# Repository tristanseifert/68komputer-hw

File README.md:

# 68komputer Hardware
Hardware designs for the 68komputer.

You can find the related software [in this repository.](https://github.com/tristanseifert/68komputer-sw)

## Old stuff
The 68008-based design I [wrote about](https://blraaz.me/hardware/2019/11/01/68komputer-it-lives.html) and some other stuff has been moved to the `old` directory. Unfortunately, those designs were done using Cadsoft EAGLE, and I no longer have access to my license for it. There are likely hardware bugs I have no way of fixing. Yay!

## License
The contents of this repo are available under the ISC license.

Previously, the material in the `old` directory was BSD licensed; you can continue to use it under the terms of this license.

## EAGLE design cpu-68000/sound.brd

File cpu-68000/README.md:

# 68000 CPU Board
This directory contains the schematic and board files for the main 68komputer CPU board, based around a 68000 operating at up to 10MHz. It combines the processor with 1M of RAM and flash ROM and some additional peripherals.

## Peripherals
In addition to the megabyte of boot ROM and RAM available on the board, the following peripherals are available:

- 32K of battery backed NVRAM, which includes a phantom RTC for time keeping
- An [XR68C681](https://www.maxlinear.com/product/interface/uarts/8-bit-vlio-uarts/xr68c681) DUART, compatible with the "legacy" Motorola 68681 part
- I²C master provided by a [PCF8584](https://www.nxp.com/products/interfaces/ic-spi-serial-interface-devices/ic-bus-controller-and-bridge-ics/ic-bus-controller:PCF8584) controller. It's used to access the I2C bus on the backplane.
- Dual SAA1099 PSG audio chips

## Backplane Interface
The backplane interface is just a buffered copy of the 68k's address and data bus, as well as many of its control signals. The direction of buffers on the CPU board are automatically controlled taking into account external bus masters.

As long as external bus masters properly implement the 68000 bus mastering, they will be entirely transparent. All read/write transactions to peripherals implemented on the CPU board itself will be broadcast on the backplane bus to allow external debugging hardware to capture these accesses.

## Programmable Logic
Many of the logic parts of the system are implemented in 22V10C GALs. See the `logic` directory for these files. They can be assembled using [galette.](https://github.com/simon-frankau/galette)

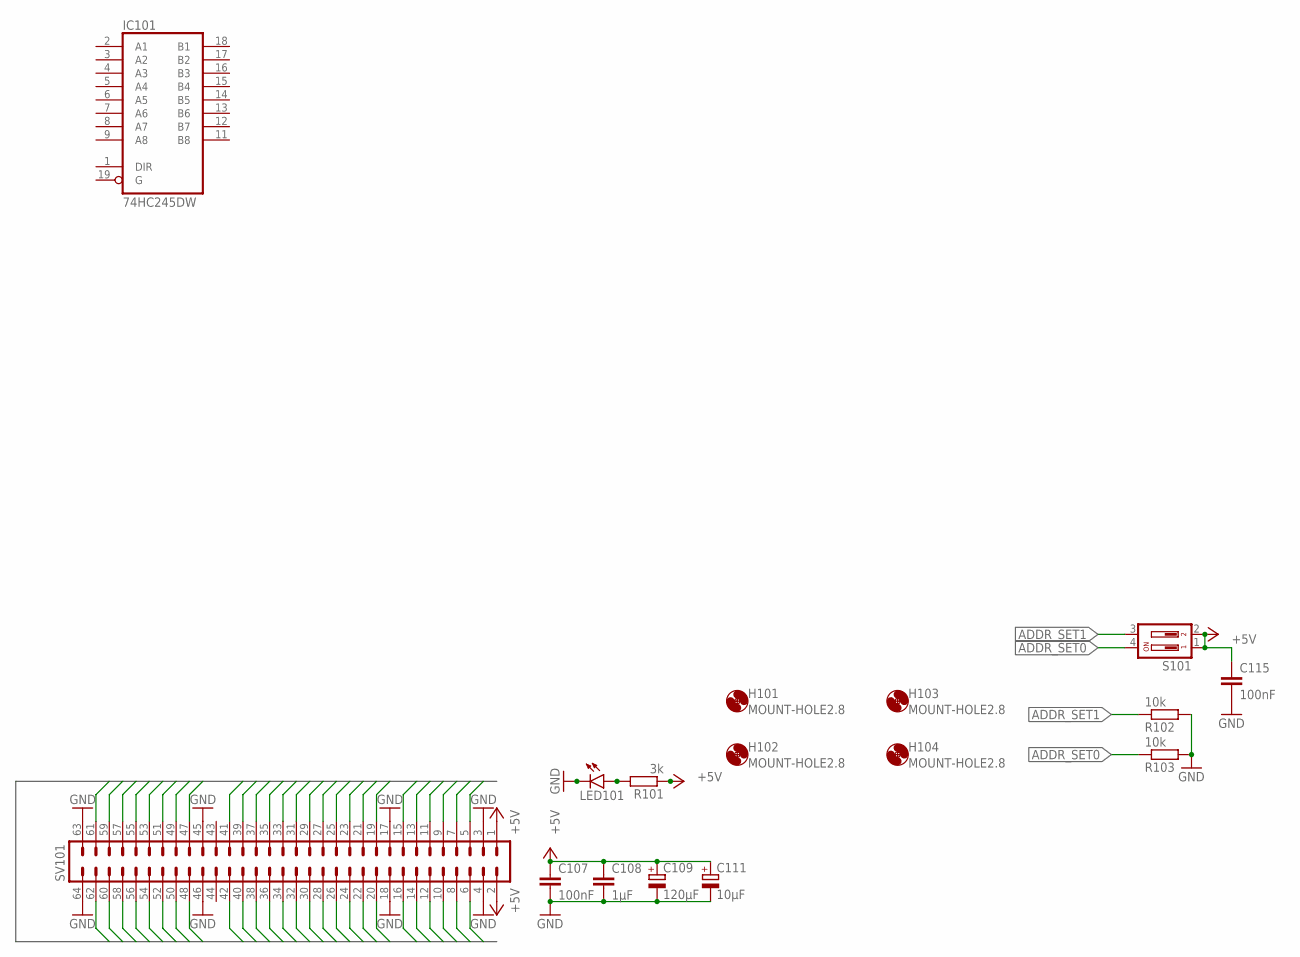
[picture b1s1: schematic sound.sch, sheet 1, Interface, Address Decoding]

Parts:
C107, C115: 100nF; C0805; MOUSER 710-885012207072
C108: 1µF; C0805; MOUSER 710-885012207078
C109: 120µF; E2,5-7; MOUSER 710-860020373007
C111: 10µF; SMC_B; MOUSER 581-TAJB106K020RNJV
H101, H102, H103, H104: MOUNT-HOLE2.8; 2,8
IC101: 74HC245DW; SO20W; MOUSER 595-SN74HC245DWR
LED101: LEDCHIPLED_1206; CHIPLED_1206; MOUSER 710-156120YS75300
R101: 3k; R2012; MOUSER 652-CR0805JW-302ELF
R102, R103: 10k; R2012; MOUSER 652-CR0805FX-1002ELF
S101: DP02; DP-02
SV101: ML64L

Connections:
!AS: SV101.13
!BG: SV101.9
!BGACK: SV101.8
!BR: SV101.7
!DTACK: SV101.10
!EXTI_A: SV101.16
!EXTI_B: SV101.15
!EXT_ID: SV101.41
!HALT: SV101.5
!LDS: SV101.11
!RESET: SV101.6
!UDS: SV101.14
+5V: C107.1, C108.1, C109.+, C111.+, C115.1, R101.1, S101.1, S101.2, SV101.1, SV101.2; also elsewhere on the board
A1: SV101.20
A2: SV101.22
A3: SV101.19
A4: SV101.24
A5: SV101.21
A6: SV101.23
A7: SV101.26
A8: SV101.25
A9: SV101.28
A10: SV101.27
A11: SV101.30
A12: SV101.29
A13: SV101.31
A14: SV101.32
A15: SV101.33
A16: SV101.34
A17: SV101.36
A18: SV101.35
A19: SV101.38
A20: SV101.37
A21: SV101.40
A22: SV101.39
A23: SV101.42
ADDR_SET0: R103.1, S101.4
ADDR_SET1: R102.1, S101.3
D0: SV101.62
D1: SV101.60
D2: SV101.58
D3: SV101.56
D4: SV101.54
D5: SV101.52
D6: SV101.50
D7: SV101.48
D8: SV101.57
D9: SV101.59
D10: SV101.61
D11: SV101.55
D12: SV101.53
D13: SV101.51
D14: SV101.49
D15: SV101.47
GND: C107.2, C108.2, C109.-, C111.-, C115.2, IC101.10 (GND), LED101.C, R102.2, R103.2, SV101.3, SV101.4, SV101.17, SV101.18, SV101.45, SV101.46, SV101.63, SV101.64; also elsewhere on the board
unnamed: LED101.A, R101.2
R/!W!: SV101.12
VCC: IC101.20 (VCC)

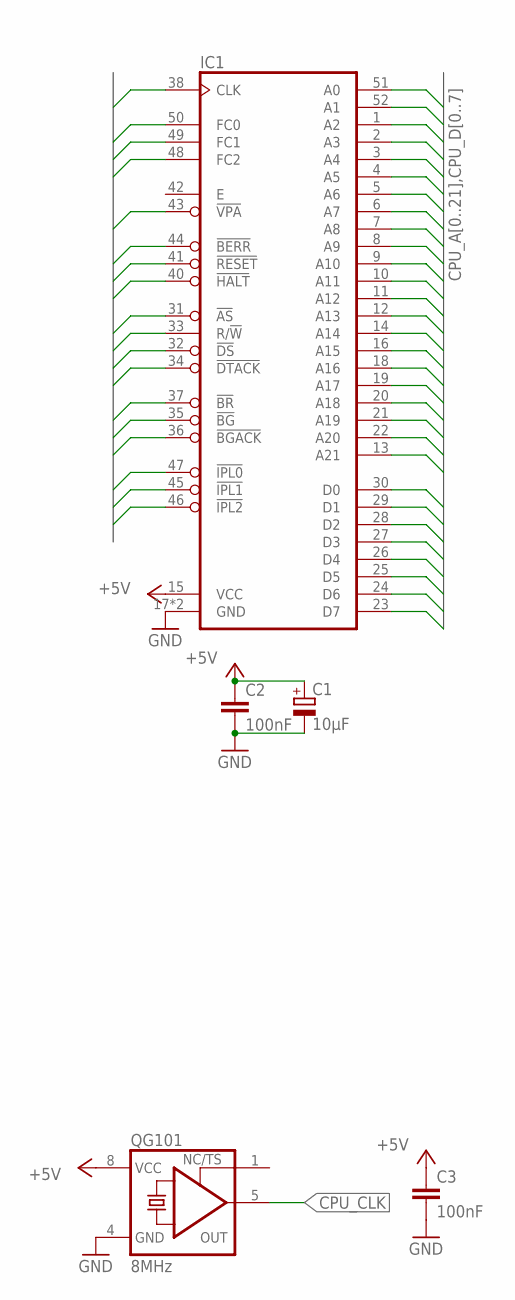
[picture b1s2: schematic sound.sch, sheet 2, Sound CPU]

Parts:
C1: 10µF; SMC_B; MOUSER 581-TAJB106K020RNJV
C2, C3: 100nF; C0805; MOUSER 710-885012207072
IC1: MC68008-PLCCPLCC52-SOCKET; PLCC52-S
QG101: 8MHz; DIL08S; MOUSER 774-MXO45HS-3C-8.0

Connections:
!CPU_AS: IC1.31 (!AS)
!CPU_BERR: IC1.44 (!BERR)
!CPU_BG: IC1.35 (!BG)
!CPU_BGACK: IC1.36 (!BGACK)
!CPU_BR: IC1.37 (!BR)
!CPU_DS: IC1.32 (!DS)
!CPU_DTACK: IC1.34 (!DTACK)
!CPU_HALT: IC1.40 (!HALT)
!CPU_IPL0: IC1.47 (!IPL0)
!CPU_IPL1: IC1.45 (!IPL1)
!CPU_IPL2: IC1.46 (!IPL2)
!CPU_RESET: IC1.41 (!RESET)
!CPU_VPA: IC1.43 (!VPA)
+5V: C1.+, C2.1, C3.1, IC1.15 (VCC), QG101.8 (VCC); also elsewhere on the board
CPU_A0: IC1.51 (A0)
CPU_A1: IC1.52 (A1)
CPU_A2: IC1.1 (A2)
CPU_A3: IC1.2 (A3)
CPU_A4: IC1.3 (A4)
CPU_A5: IC1.4 (A5)
CPU_A6: IC1.5 (A6)
CPU_A7: IC1.6 (A7)
CPU_A8: IC1.7 (A8)
CPU_A9: IC1.8 (A9)
CPU_A10: IC1.9 (A10)
CPU_A11: IC1.10 (A11)
CPU_A12: IC1.11 (A12)
CPU_A13: IC1.12 (A13)
CPU_A14: IC1.14 (A14)
CPU_A15: IC1.16 (A15)
CPU_A16: IC1.18 (A16)
CPU_A17: IC1.19 (A17)
CPU_A18: IC1.20 (A18)
CPU_A19: IC1.21 (A19)
CPU_A20: IC1.22 (A20)
CPU_A21: IC1.13 (A21)
CPU_CLK: IC1.38 (CLK), QG101.5 (OUT)
CPU_D0: IC1.30 (D0)
CPU_D1: IC1.29 (D1)
CPU_D2: IC1.28 (D2)
CPU_D3: IC1.27 (D3)
CPU_D4: IC1.26 (D4)
CPU_D5: IC1.25 (D5)
CPU_D6: IC1.24 (D6)
CPU_D7: IC1.23 (D7)
CPU_FC0: IC1.50 (FC0)
CPU_FC1: IC1.49 (FC1)
CPU_FC2: IC1.48 (FC2)
CPU_R/!W!: IC1.33 (R/!W)
GND: C1.-, C2.2, C3.2, IC1.17 (GND), IC1.39 (GND), QG101.4 (GND); also elsewhere on the board

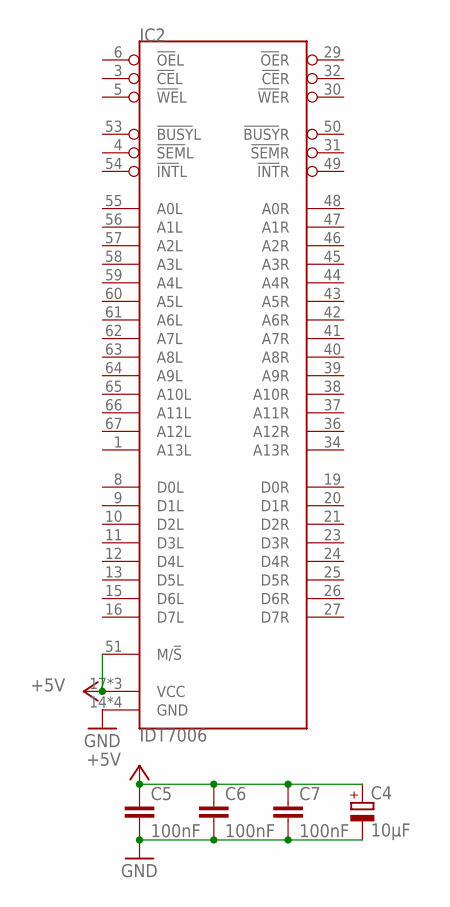
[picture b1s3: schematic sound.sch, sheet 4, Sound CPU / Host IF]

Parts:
C4: 10µF; SMC_B; MOUSER 581-TAJB106K020RNJV
C5, C6, C7: 100nF; C0805; MOUSER 710-885012207072
IC2: IDT7006; PLCC68-S

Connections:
+5V: C4.+, C5.1, C6.1, C7.1, IC2.17 (VCC), IC2.22 (VCC), IC2.51 (M/!S!), IC2.68 (VCC); also elsewhere on the board
GND: C4.-, C5.2, C6.2, C7.2, IC2.14 (GND), IC2.18 (GND), IC2.35 (GND), IC2.52 (GND); also elsewhere on the board

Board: 2 copper layers, 26 parts (3 on the bottom side), 6 nets, no tracks yet.

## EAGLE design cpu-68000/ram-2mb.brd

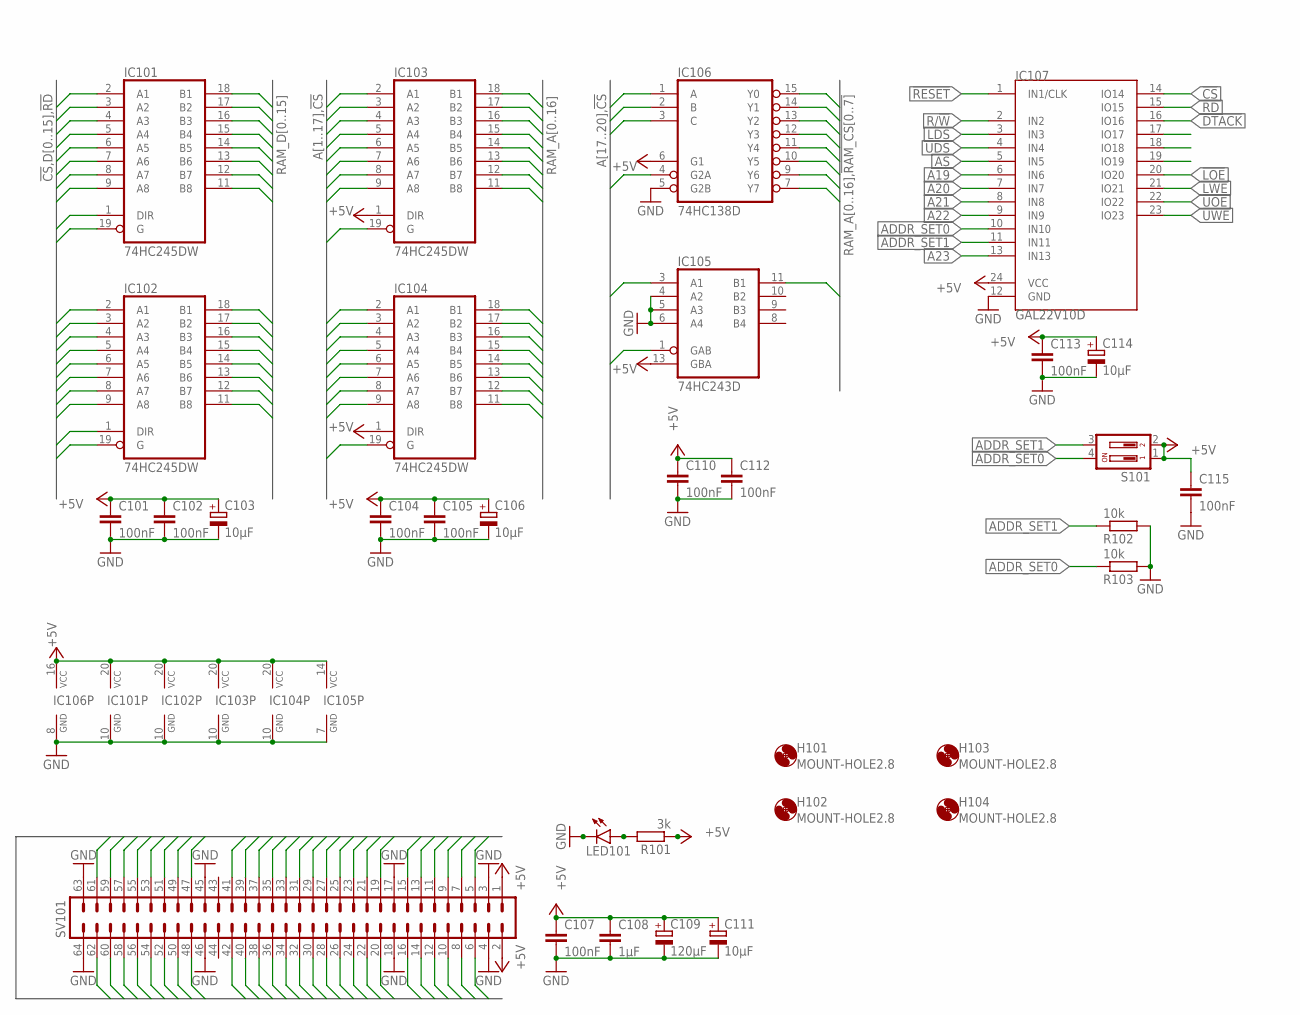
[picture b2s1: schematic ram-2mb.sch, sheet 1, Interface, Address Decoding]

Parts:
C101, C102, C104, C105, C107, C110, C112, C113, C115: 100nF; C0805; MOUSER 710-885012207072
C103, C106, C111, C114: 10µF; SMC_B; MOUSER 581-TAJB106K020RNJV
C108: 1µF; C0805; MOUSER 710-885012207078
C109: 120µF; E2,5-7; MOUSER 710-860020373007
H101, H102, H103, H104: MOUNT-HOLE2.8; 2,8
IC101, IC102, IC103, IC104: 74HC245DW; SO20W; MOUSER 595-SN74HC245DWR
IC105: 74HC243D; SO14; MOUSER 595-CD74HC243M96
IC106: 74HC138D; SO16; MOUSER 595-SN74HC138DG4
IC107: GAL22V10D; DIL24S; MOUSER_SOCKET 575-1104732441001000
LED101: LEDCHIPLED_1206; CHIPLED_1206; MOUSER 710-156120YS75300
R101: 3k; R2012; MOUSER 652-CR0805JW-302ELF
R102, R103: 10k; R2012; MOUSER 652-CR0805FX-1002ELF
S101: DP02; DP-02
SV101: ML64L

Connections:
!AS: IC107.5 (IN5), SV101.13
!BG: SV101.9
!BGACK: SV101.8
!BR: SV101.7
!CS: IC101.19 (G), IC102.19 (G), IC103.19 (G), IC104.19 (G), IC105.1 (GAB), IC106.4 (G2A), IC107.14 (IO14)
!DTACK: IC107.16 (IO16), SV101.10
!EXTI_A: SV101.16
!EXTI_B: SV101.15
!EXT_ID: SV101.41
!HALT: SV101.5
!LDS: IC107.3 (IN3), SV101.11
!LOE: IC107.20 (IO20); also elsewhere on the board
!LWE: IC107.21 (IO21); also elsewhere on the board
!RAM_CS0: IC106.15 (Y0); also elsewhere on the board
!RAM_CS1: IC106.14 (Y1); also elsewhere on the board
!RAM_CS2: IC106.13 (Y2); also elsewhere on the board
!RAM_CS3: IC106.12 (Y3); also elsewhere on the board
!RAM_CS4: IC106.11 (Y4); also elsewhere on the board
!RAM_CS5: IC106.10 (Y5); also elsewhere on the board
!RAM_CS6: IC106.9 (Y6); also elsewhere on the board
!RAM_CS7: IC106.7 (Y7); also elsewhere on the board
!RD: IC101.1 (DIR), IC102.1 (DIR), IC107.15 (IO15)
!RESET: IC107.1 (IN1/CLK), SV101.6
!UDS: IC107.4 (IN4), SV101.14
!UOE: IC107.22 (IO22); also elsewhere on the board
!UWE: IC107.23 (IO23); also elsewhere on the board
+5V: C101.1, C102.1, C103.+, C104.1, C105.1, C106.+, C107.1, C108.1, C109.+, C110.1, C111.+, C112.1, C113.1, C114.+, C115.1, IC101.20 (VCC), IC102.20 (VCC), IC103.1 (DIR), IC103.20 (VCC), IC104.1 (DIR), IC104.20 (VCC), IC105.13 (GBA), IC105.14 (VCC), IC106.6 (G1), IC106.16 (VCC), IC107.24 (VCC), R101.1, S101.1, S101.2, SV101.1, SV101.2; also elsewhere on the board
A1: IC103.2 (A1), SV101.20
A2: IC103.3 (A2), SV101.22
A3: IC103.4 (A3), SV101.19
A4: IC103.5 (A4), SV101.24
A5: IC103.6 (A5), SV101.21
A6: IC103.7 (A6), SV101.23
A7: IC103.8 (A7), SV101.26
A8: IC103.9 (A8), SV101.25
A9: IC104.2 (A1), SV101.28
A10: IC104.3 (A2), SV101.27
A11: IC104.4 (A3), SV101.30
A12: IC104.5 (A4), SV101.29
A13: IC104.6 (A5), SV101.31
A14: IC104.7 (A6), SV101.32
A15: IC104.8 (A7), SV101.33
A16: IC104.9 (A8), SV101.34
A17: IC105.3 (A1), SV101.36
A18: IC106.1 (A), SV101.35
A19: IC106.2 (B), IC107.6 (IN6), SV101.38
A20: IC106.3 (C), IC107.7 (IN7), SV101.37
A21: IC107.8 (IN8), SV101.40
A22: IC107.9 (IN9), SV101.39
A23: IC107.13 (IN13), SV101.42
ADDR_SET0: IC107.10 (IN10), R103.1, S101.4
ADDR_SET1: IC107.11 (IN11), R102.1, S101.3
D0: IC101.2 (A1), SV101.62
D1: IC101.3 (A2), SV101.60
D2: IC101.4 (A3), SV101.58
D3: IC101.5 (A4), SV101.56
D4: IC101.6 (A5), SV101.54
D5: IC101.7 (A6), SV101.52
D6: IC101.8 (A7), SV101.50
D7: IC101.9 (A8), SV101.48
D8: IC102.2 (A1), SV101.57
D9: IC102.3 (A2), SV101.59
D10: IC102.4 (A3), SV101.61
D11: IC102.5 (A4), SV101.55
D12: IC102.6 (A5), SV101.53
D13: IC102.7 (A6), SV101.51
D14: IC102.8 (A7), SV101.49
D15: IC102.9 (A8), SV101.47
GND: C101.2, C102.2, C103.-, C104.2, C105.2, C106.-, C107.2, C108.2, C109.-, C110.2, C111.-, C112.2, C113.2, C114.-, C115.2, IC101.10 (GND), IC102.10 (GND), IC103.10 (GND), IC104.10 (GND), IC105.4 (A2), IC105.5 (A3), IC105.6 (A4), IC105.7 (GND), IC106.5 (G2B), IC106.8 (GND), IC107.12 (GND), LED101.C, R102.2, R103.2, SV101.3, SV101.4, SV101.17, SV101.18, SV101.45, SV101.46, SV101.63, SV101.64; also elsewhere on the board
unnamed: LED101.A, R101.2
R/!W!: IC107.2 (IN2), SV101.12
RAM_A0: IC103.18 (B1); also elsewhere on the board
RAM_A1: IC103.17 (B2); also elsewhere on the board
RAM_A2: IC103.16 (B3); also elsewhere on the board
RAM_A3: IC103.15 (B4); also elsewhere on the board
RAM_A4: IC103.14 (B5); also elsewhere on the board
RAM_A5: IC103.13 (B6); also elsewhere on the board
RAM_A6: IC103.12 (B7); also elsewhere on the board
RAM_A7: IC103.11 (B8); also elsewhere on the board
RAM_A8: IC104.18 (B1); also elsewhere on the board
RAM_A9: IC104.17 (B2); also elsewhere on the board
RAM_A10: IC104.16 (B3); also elsewhere on the board
RAM_A11: IC104.15 (B4); also elsewhere on the board
RAM_A12: IC104.14 (B5); also elsewhere on the board
RAM_A13: IC104.13 (B6); also elsewhere on the board
RAM_A14: IC104.12 (B7); also elsewhere on the board
RAM_A15: IC104.11 (B8); also elsewhere on the board
RAM_A16: IC105.11 (B1); also elsewhere on the board
RAM_D0: IC101.18 (B1); also elsewhere on the board
RAM_D1: IC101.17 (B2); also elsewhere on the board
RAM_D2: IC101.16 (B3); also elsewhere on the board
RAM_D3: IC101.15 (B4); also elsewhere on the board
RAM_D4: IC101.14 (B5); also elsewhere on the board
RAM_D5: IC101.13 (B6); also elsewhere on the board
RAM_D6: IC101.12 (B7); also elsewhere on the board
RAM_D7: IC101.11 (B8); also elsewhere on the board
RAM_D8: IC102.18 (B1); also elsewhere on the board
RAM_D9: IC102.17 (B2); also elsewhere on the board
RAM_D10: IC102.16 (B3); also elsewhere on the board
RAM_D11: IC102.15 (B4); also elsewhere on the board
RAM_D12: IC102.14 (B5); also elsewhere on the board
RAM_D13: IC102.13 (B6); also elsewhere on the board
RAM_D14: IC102.12 (B7); also elsewhere on the board
RAM_D15: IC102.11 (B8); also elsewhere on the board

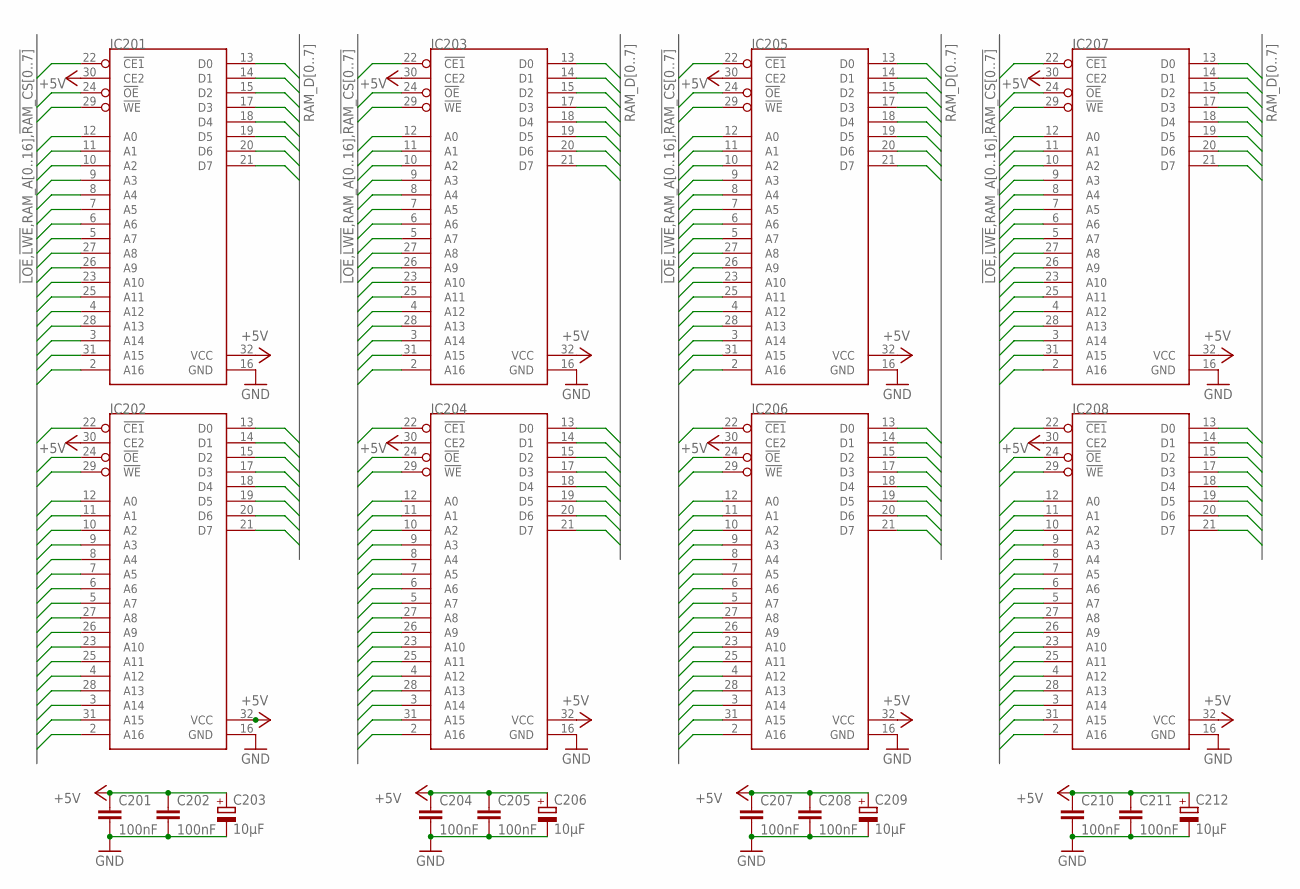
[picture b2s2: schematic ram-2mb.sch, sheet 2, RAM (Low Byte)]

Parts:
C201, C202, C204, C205, C207, C208, C210, C211: 100nF; C0805; MOUSER 710-885012207072
C203, C206, C209, C212: 10µF; SMC_B; MOUSER 581-TAJB106K020RNJV
IC201, IC202, IC203, IC204, IC205, IC206, IC207, IC208: CY62128BSOIC32-450; SOIC127P1412X299-32N

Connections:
!LOE: IC201.24 (!OE), IC202.24 (!OE), IC203.24 (!OE), IC204.24 (!OE), IC205.24 (!OE), IC206.24 (!OE), IC207.24 (!OE), IC208.24 (!OE); also elsewhere on the board
!LWE: IC201.29 (!WE), IC202.29 (!WE), IC203.29 (!WE), IC204.29 (!WE), IC205.29 (!WE), IC206.29 (!WE), IC207.29 (!WE), IC208.29 (!WE); also elsewhere on the board
!RAM_CS0: IC201.22 (!CE1); also elsewhere on the board
!RAM_CS1: IC202.22 (!CE1); also elsewhere on the board
!RAM_CS2: IC203.22 (!CE1); also elsewhere on the board
!RAM_CS3: IC204.22 (!CE1); also elsewhere on the board
!RAM_CS4: IC205.22 (!CE1); also elsewhere on the board
!RAM_CS5: IC206.22 (!CE1); also elsewhere on the board
!RAM_CS6: IC207.22 (!CE1); also elsewhere on the board
!RAM_CS7: IC208.22 (!CE1); also elsewhere on the board
+5V: C201.1, C202.1, C203.+, C204.1, C205.1, C206.+, C207.1, C208.1, C209.+, C210.1, C211.1, C212.+, IC201.30 (CE2), IC201.32 (VCC), IC202.30 (CE2), IC202.32 (VCC), IC203.30 (CE2), IC203.32 (VCC), IC204.30 (CE2), IC204.32 (VCC), IC205.30 (CE2), IC205.32 (VCC), IC206.30 (CE2), IC206.32 (VCC), IC207.30 (CE2), IC207.32 (VCC), IC208.30 (CE2), IC208.32 (VCC); also elsewhere on the board
GND: C201.2, C202.2, C203.-, C204.2, C205.2, C206.-, C207.2, C208.2, C209.-, C210.2, C211.2, C212.-, IC201.16 (GND), IC202.16 (GND), IC203.16 (GND), IC204.16 (GND), IC205.16 (GND), IC206.16 (GND), IC207.16 (GND), IC208.16 (GND); also elsewhere on the board
RAM_A0: IC201.12 (A0), IC202.12 (A0), IC203.12 (A0), IC204.12 (A0), IC205.12 (A0), IC206.12 (A0), IC207.12 (A0), IC208.12 (A0); also elsewhere on the board
RAM_A1: IC201.11 (A1), IC202.11 (A1), IC203.11 (A1), IC204.11 (A1), IC205.11 (A1), IC206.11 (A1), IC207.11 (A1), IC208.11 (A1); also elsewhere on the board
RAM_A2: IC201.10 (A2), IC202.10 (A2), IC203.10 (A2), IC204.10 (A2), IC205.10 (A2), IC206.10 (A2), IC207.10 (A2), IC208.10 (A2); also elsewhere on the board
RAM_A3: IC201.9 (A3), IC202.9 (A3), IC203.9 (A3), IC204.9 (A3), IC205.9 (A3), IC206.9 (A3), IC207.9 (A3), IC208.9 (A3); also elsewhere on the board
RAM_A4: IC201.8 (A4), IC202.8 (A4), IC203.8 (A4), IC204.8 (A4), IC205.8 (A4), IC206.8 (A4), IC207.8 (A4), IC208.8 (A4); also elsewhere on the board
RAM_A5: IC201.7 (A5), IC202.7 (A5), IC203.7 (A5), IC204.7 (A5), IC205.7 (A5), IC206.7 (A5), IC207.7 (A5), IC208.7 (A5); also elsewhere on the board
RAM_A6: IC201.6 (A6), IC202.6 (A6), IC203.6 (A6), IC204.6 (A6), IC205.6 (A6), IC206.6 (A6), IC207.6 (A6), IC208.6 (A6); also elsewhere on the board
RAM_A7: IC201.5 (A7), IC202.5 (A7), IC203.5 (A7), IC204.5 (A7), IC205.5 (A7), IC206.5 (A7), IC207.5 (A7), IC208.5 (A7); also elsewhere on the board
RAM_A8: IC201.27 (A8), IC202.27 (A8), IC203.27 (A8), IC204.27 (A8), IC205.27 (A8), IC206.27 (A8), IC207.27 (A8), IC208.27 (A8); also elsewhere on the board
RAM_A9: IC201.26 (A9), IC202.26 (A9), IC203.26 (A9), IC204.26 (A9), IC205.26 (A9), IC206.26 (A9), IC207.26 (A9), IC208.26 (A9); also elsewhere on the board
RAM_A10: IC201.23 (A10), IC202.23 (A10), IC203.23 (A10), IC204.23 (A10), IC205.23 (A10), IC206.23 (A10), IC207.23 (A10), IC208.23 (A10); also elsewhere on the board
RAM_A11: IC201.25 (A11), IC202.25 (A11), IC203.25 (A11), IC204.25 (A11), IC205.25 (A11), IC206.25 (A11), IC207.25 (A11), IC208.25 (A11); also elsewhere on the board
RAM_A12: IC201.4 (A12), IC202.4 (A12), IC203.4 (A12), IC204.4 (A12), IC205.4 (A12), IC206.4 (A12), IC207.4 (A12), IC208.4 (A12); also elsewhere on the board
RAM_A13: IC201.28 (A13), IC202.28 (A13), IC203.28 (A13), IC204.28 (A13), IC205.28 (A13), IC206.28 (A13), IC207.28 (A13), IC208.28 (A13); also elsewhere on the board
RAM_A14: IC201.3 (A14), IC202.3 (A14), IC203.3 (A14), IC204.3 (A14), IC205.3 (A14), IC206.3 (A14), IC207.3 (A14), IC208.3 (A14); also elsewhere on the board
RAM_A15: IC201.31 (A15), IC202.31 (A15), IC203.31 (A15), IC204.31 (A15), IC205.31 (A15), IC206.31 (A15), IC207.31 (A15), IC208.31 (A15); also elsewhere on the board
RAM_A16: IC201.2 (A16), IC202.2 (A16), IC203.2 (A16), IC204.2 (A16), IC205.2 (A16), IC206.2 (A16), IC207.2 (A16), IC208.2 (A16); also elsewhere on the board
RAM_D0: IC201.13 (D0), IC202.13 (D0), IC203.13 (D0), IC204.13 (D0), IC205.13 (D0), IC206.13 (D0), IC207.13 (D0), IC208.13 (D0); also elsewhere on the board
RAM_D1: IC201.14 (D1), IC202.14 (D1), IC203.14 (D1), IC204.14 (D1), IC205.14 (D1), IC206.14 (D1), IC207.14 (D1), IC208.14 (D1); also elsewhere on the board
RAM_D2: IC201.15 (D2), IC202.15 (D2), IC203.15 (D2), IC204.15 (D2), IC205.15 (D2), IC206.15 (D2), IC207.15 (D2), IC208.15 (D2); also elsewhere on the board
RAM_D3: IC201.17 (D3), IC202.17 (D3), IC203.17 (D3), IC204.17 (D3), IC205.17 (D3), IC206.17 (D3), IC207.17 (D3), IC208.17 (D3); also elsewhere on the board
RAM_D4: IC201.18 (D4), IC202.18 (D4), IC203.18 (D4), IC204.18 (D4), IC205.18 (D4), IC206.18 (D4), IC207.18 (D4), IC208.18 (D4); also elsewhere on the board
RAM_D5: IC201.19 (D5), IC202.19 (D5), IC203.19 (D5), IC204.19 (D5), IC205.19 (D5), IC206.19 (D5), IC207.19 (D5), IC208.19 (D5); also elsewhere on the board
RAM_D6: IC201.20 (D6), IC202.20 (D6), IC203.20 (D6), IC204.20 (D6), IC205.20 (D6), IC206.20 (D6), IC207.20 (D6), IC208.20 (D6); also elsewhere on the board
RAM_D7: IC201.21 (D7), IC202.21 (D7), IC203.21 (D7), IC204.21 (D7), IC205.21 (D7), IC206.21 (D7), IC207.21 (D7), IC208.21 (D7); also elsewhere on the board

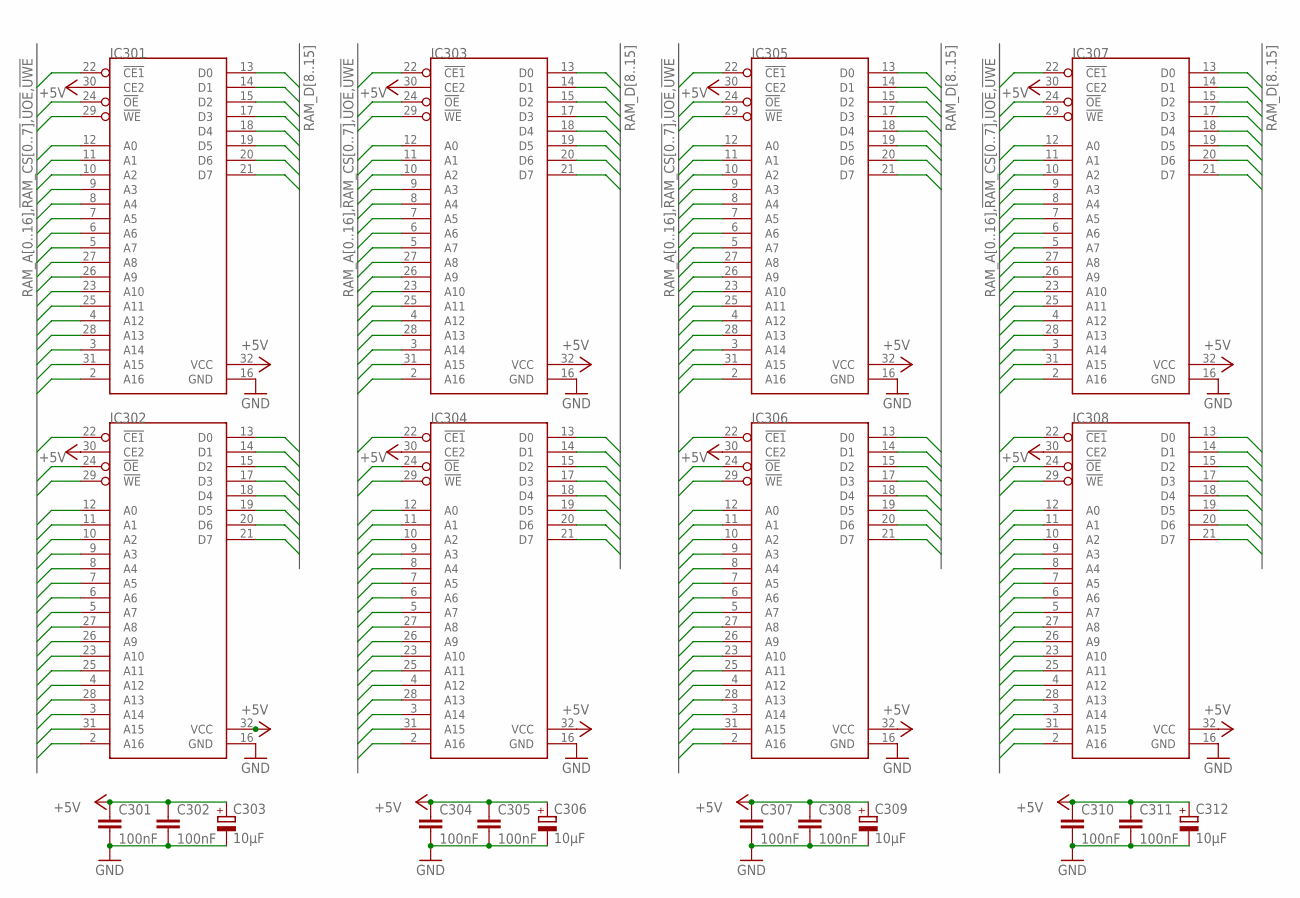
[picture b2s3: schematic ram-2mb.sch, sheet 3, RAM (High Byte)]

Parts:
C301, C302, C304, C305, C307, C308, C310, C311: 100nF; C0805; MOUSER 710-885012207072
C303, C306, C309, C312: 10µF; SMC_B; MOUSER 581-TAJB106K020RNJV
IC301, IC302, IC303, IC304, IC305, IC306, IC307, IC308: CY62128BSOIC32-450; SOIC127P1412X299-32N

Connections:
!RAM_CS0: IC301.22 (!CE1); also elsewhere on the board
!RAM_CS1: IC302.22 (!CE1); also elsewhere on the board
!RAM_CS2: IC303.22 (!CE1); also elsewhere on the board
!RAM_CS3: IC304.22 (!CE1); also elsewhere on the board
!RAM_CS4: IC305.22 (!CE1); also elsewhere on the board
!RAM_CS5: IC306.22 (!CE1); also elsewhere on the board
!RAM_CS6: IC307.22 (!CE1); also elsewhere on the board
!RAM_CS7: IC308.22 (!CE1); also elsewhere on the board
!UOE: IC301.24 (!OE), IC302.24 (!OE), IC303.24 (!OE), IC304.24 (!OE), IC305.24 (!OE), IC306.24 (!OE), IC307.24 (!OE), IC308.24 (!OE); also elsewhere on the board
!UWE: IC301.29 (!WE), IC302.29 (!WE), IC303.29 (!WE), IC304.29 (!WE), IC305.29 (!WE), IC306.29 (!WE), IC307.29 (!WE), IC308.29 (!WE); also elsewhere on the board
+5V: C301.1, C302.1, C303.+, C304.1, C305.1, C306.+, C307.1, C308.1, C309.+, C310.1, C311.1, C312.+, IC301.30 (CE2), IC301.32 (VCC), IC302.30 (CE2), IC302.32 (VCC), IC303.30 (CE2), IC303.32 (VCC), IC304.30 (CE2), IC304.32 (VCC), IC305.30 (CE2), IC305.32 (VCC), IC306.30 (CE2), IC306.32 (VCC), IC307.30 (CE2), IC307.32 (VCC), IC308.30 (CE2), IC308.32 (VCC); also elsewhere on the board
GND: C301.2, C302.2, C303.-, C304.2, C305.2, C306.-, C307.2, C308.2, C309.-, C310.2, C311.2, C312.-, IC301.16 (GND), IC302.16 (GND), IC303.16 (GND), IC304.16 (GND), IC305.16 (GND), IC306.16 (GND), IC307.16 (GND), IC308.16 (GND); also elsewhere on the board
RAM_A0: IC301.12 (A0), IC302.12 (A0), IC303.12 (A0), IC304.12 (A0), IC305.12 (A0), IC306.12 (A0), IC307.12 (A0), IC308.12 (A0); also elsewhere on the board
RAM_A1: IC301.11 (A1), IC302.11 (A1), IC303.11 (A1), IC304.11 (A1), IC305.11 (A1), IC306.11 (A1), IC307.11 (A1), IC308.11 (A1); also elsewhere on the board
RAM_A2: IC301.10 (A2), IC302.10 (A2), IC303.10 (A2), IC304.10 (A2), IC305.10 (A2), IC306.10 (A2), IC307.10 (A2), IC308.10 (A2); also elsewhere on the board
RAM_A3: IC301.9 (A3), IC302.9 (A3), IC303.9 (A3), IC304.9 (A3), IC305.9 (A3), IC306.9 (A3), IC307.9 (A3), IC308.9 (A3); also elsewhere on the board
RAM_A4: IC301.8 (A4), IC302.8 (A4), IC303.8 (A4), IC304.8 (A4), IC305.8 (A4), IC306.8 (A4), IC307.8 (A4), IC308.8 (A4); also elsewhere on the board
RAM_A5: IC301.7 (A5), IC302.7 (A5), IC303.7 (A5), IC304.7 (A5), IC305.7 (A5), IC306.7 (A5), IC307.7 (A5), IC308.7 (A5); also elsewhere on the board
RAM_A6: IC301.6 (A6), IC302.6 (A6), IC303.6 (A6), IC304.6 (A6), IC305.6 (A6), IC306.6 (A6), IC307.6 (A6), IC308.6 (A6); also elsewhere on the board
RAM_A7: IC301.5 (A7), IC302.5 (A7), IC303.5 (A7), IC304.5 (A7), IC305.5 (A7), IC306.5 (A7), IC307.5 (A7), IC308.5 (A7); also elsewhere on the board
RAM_A8: IC301.27 (A8), IC302.27 (A8), IC303.27 (A8), IC304.27 (A8), IC305.27 (A8), IC306.27 (A8), IC307.27 (A8), IC308.27 (A8); also elsewhere on the board
RAM_A9: IC301.26 (A9), IC302.26 (A9), IC303.26 (A9), IC304.26 (A9), IC305.26 (A9), IC306.26 (A9), IC307.26 (A9), IC308.26 (A9); also elsewhere on the board
RAM_A10: IC301.23 (A10), IC302.23 (A10), IC303.23 (A10), IC304.23 (A10), IC305.23 (A10), IC306.23 (A10), IC307.23 (A10), IC308.23 (A10); also elsewhere on the board
RAM_A11: IC301.25 (A11), IC302.25 (A11), IC303.25 (A11), IC304.25 (A11), IC305.25 (A11), IC306.25 (A11), IC307.25 (A11), IC308.25 (A11); also elsewhere on the board
RAM_A12: IC301.4 (A12), IC302.4 (A12), IC303.4 (A12), IC304.4 (A12), IC305.4 (A12), IC306.4 (A12), IC307.4 (A12), IC308.4 (A12); also elsewhere on the board
RAM_A13: IC301.28 (A13), IC302.28 (A13), IC303.28 (A13), IC304.28 (A13), IC305.28 (A13), IC306.28 (A13), IC307.28 (A13), IC308.28 (A13); also elsewhere on the board
RAM_A14: IC301.3 (A14), IC302.3 (A14), IC303.3 (A14), IC304.3 (A14), IC305.3 (A14), IC306.3 (A14), IC307.3 (A14), IC308.3 (A14); also elsewhere on the board
RAM_A15: IC301.31 (A15), IC302.31 (A15), IC303.31 (A15), IC304.31 (A15), IC305.31 (A15), IC306.31 (A15), IC307.31 (A15), IC308.31 (A15); also elsewhere on the board
RAM_A16: IC301.2 (A16), IC302.2 (A16), IC303.2 (A16), IC304.2 (A16), IC305.2 (A16), IC306.2 (A16), IC307.2 (A16), IC308.2 (A16); also elsewhere on the board
RAM_D8: IC301.13 (D0), IC302.13 (D0), IC303.13 (D0), IC304.13 (D0), IC305.13 (D0), IC306.13 (D0), IC307.13 (D0), IC308.13 (D0); also elsewhere on the board
RAM_D9: IC301.14 (D1), IC302.14 (D1), IC303.14 (D1), IC304.14 (D1), IC305.14 (D1), IC306.14 (D1), IC307.14 (D1), IC308.14 (D1); also elsewhere on the board
RAM_D10: IC301.15 (D2), IC302.15 (D2), IC303.15 (D2), IC304.15 (D2), IC305.15 (D2), IC306.15 (D2), IC307.15 (D2), IC308.15 (D2); also elsewhere on the board
RAM_D11: IC301.17 (D3), IC302.17 (D3), IC303.17 (D3), IC304.17 (D3), IC305.17 (D3), IC306.17 (D3), IC307.17 (D3), IC308.17 (D3); also elsewhere on the board
RAM_D12: IC301.18 (D4), IC302.18 (D4), IC303.18 (D4), IC304.18 (D4), IC305.18 (D4), IC306.18 (D4), IC307.18 (D4), IC308.18 (D4); also elsewhere on the board
RAM_D13: IC301.19 (D5), IC302.19 (D5), IC303.19 (D5), IC304.19 (D5), IC305.19 (D5), IC306.19 (D5), IC307.19 (D5), IC308.19 (D5); also elsewhere on the board
RAM_D14: IC301.20 (D6), IC302.20 (D6), IC303.20 (D6), IC304.20 (D6), IC305.20 (D6), IC306.20 (D6), IC307.20 (D6), IC308.20 (D6); also elsewhere on the board
RAM_D15: IC301.21 (D7), IC302.21 (D7), IC303.21 (D7), IC304.21 (D7), IC305.21 (D7), IC306.21 (D7), IC307.21 (D7), IC308.21 (D7); also elsewhere on the board

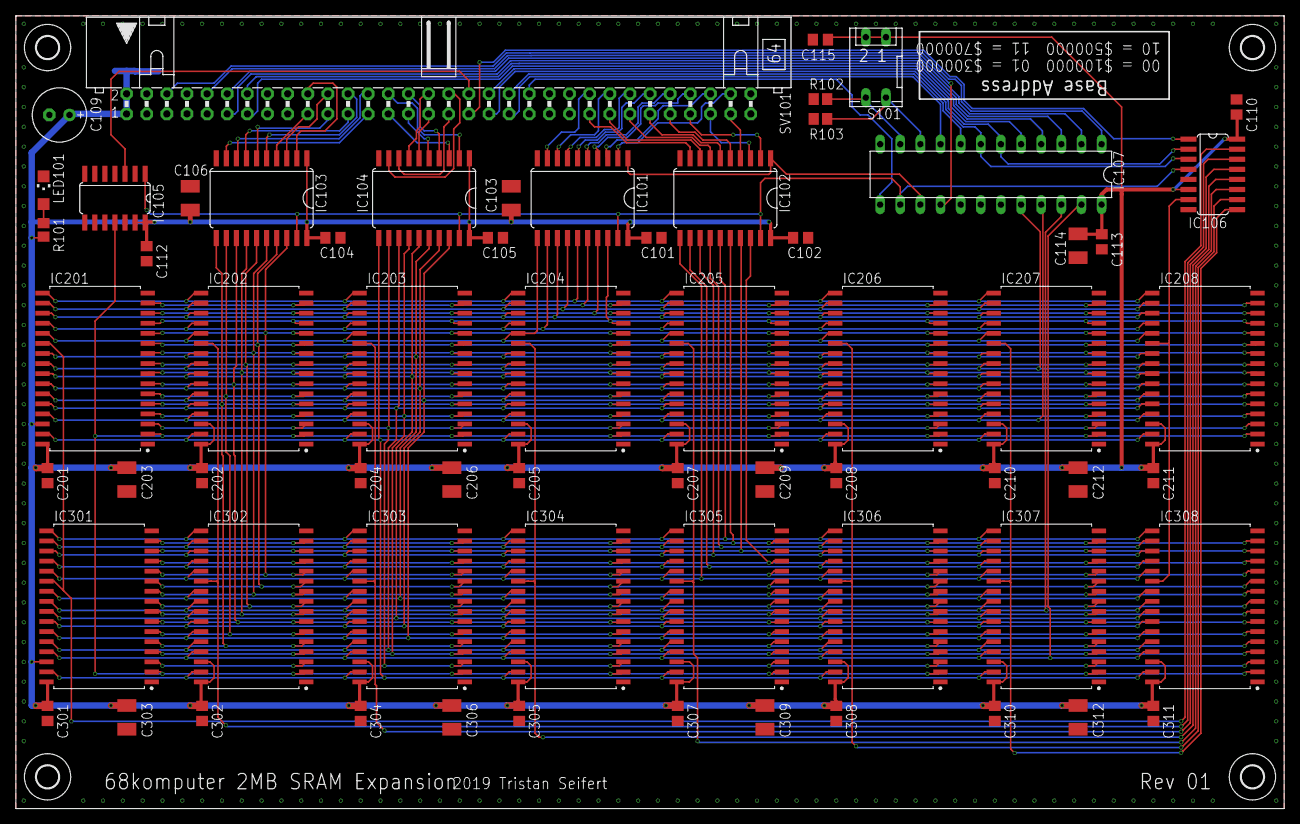
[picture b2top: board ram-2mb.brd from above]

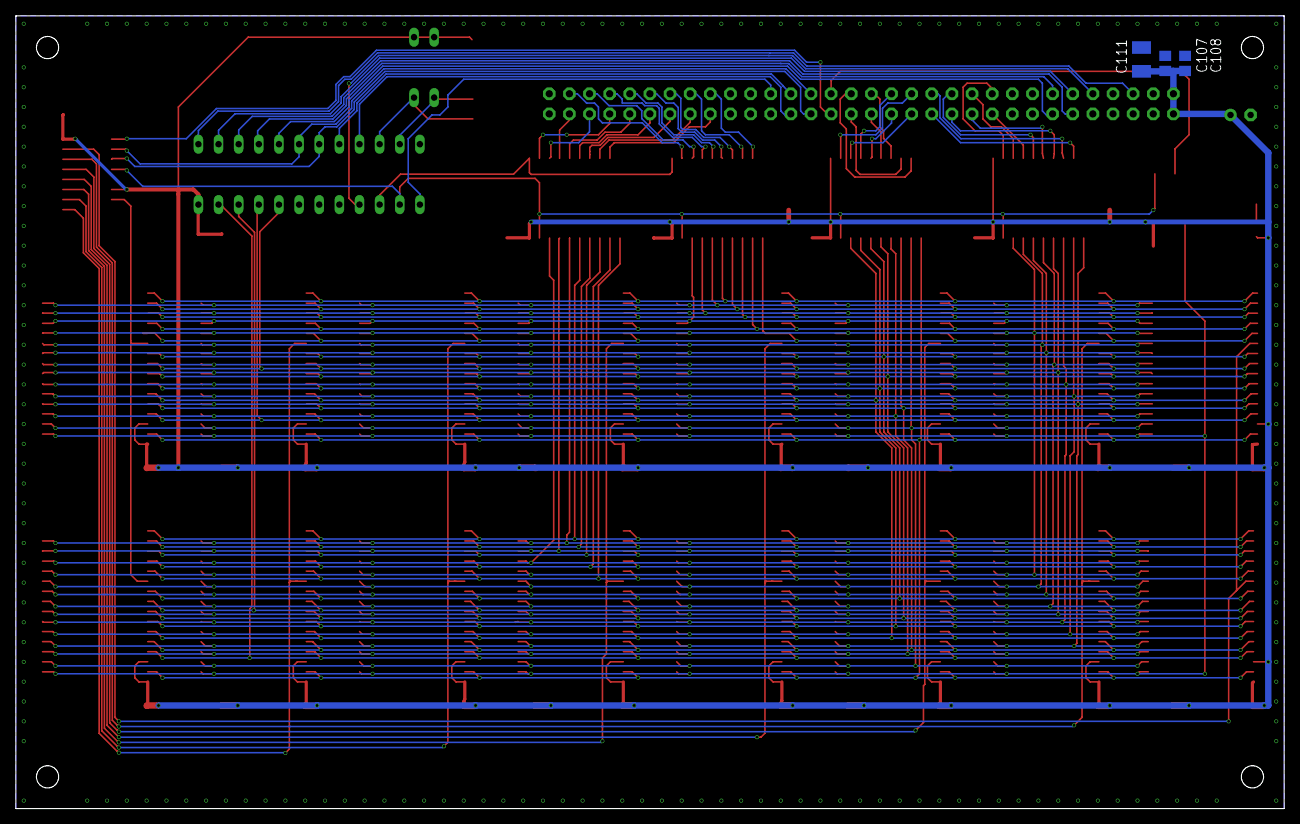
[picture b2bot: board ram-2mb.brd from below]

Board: 2 copper layers, 160.0 x 100.0 mm, 72 parts (3 on the bottom side), 97 nets.

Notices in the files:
cpu-68000/cpu-68000.brd:
(c) 2019 Tristan Seifert
parts and their libraries:
SparkFun-Connectors: Licensing: Creative Commons ShareAlike 4.0 International - https://creativecommons.org/licenses/by-sa/4.0
